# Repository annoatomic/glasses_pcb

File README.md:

KICAD projects saved in: flex_mems

flex_aufsatz project in: flex_mems
                      -->flex_aufsatz

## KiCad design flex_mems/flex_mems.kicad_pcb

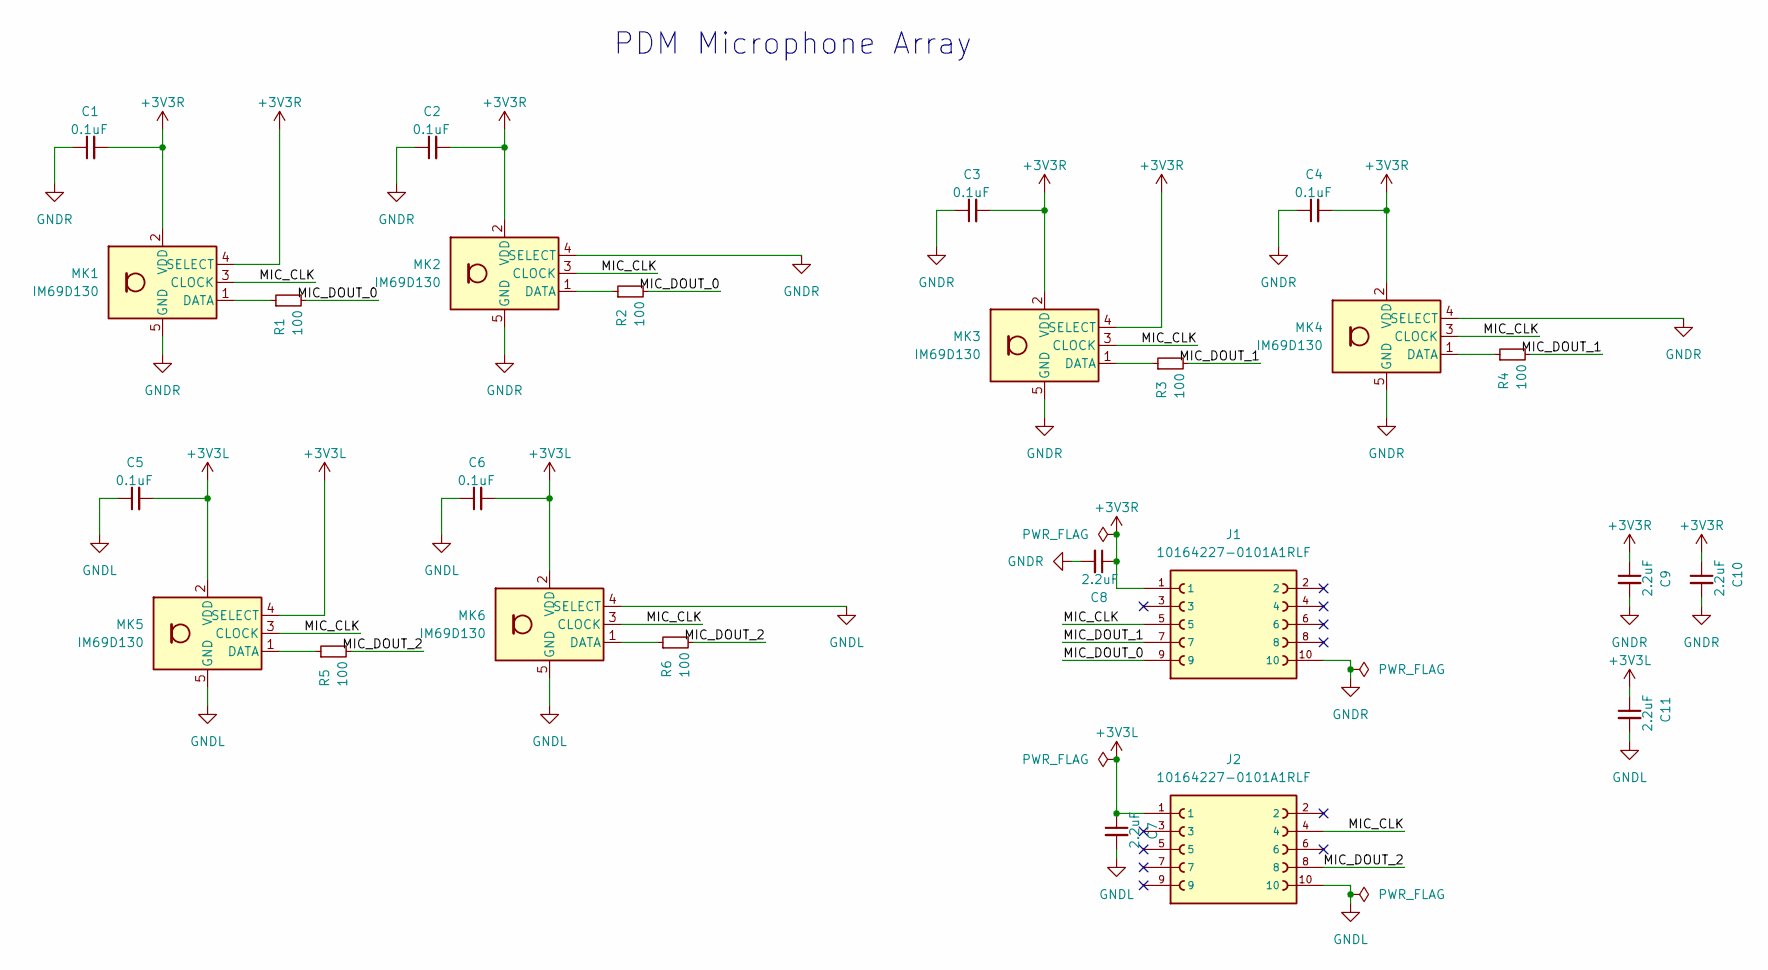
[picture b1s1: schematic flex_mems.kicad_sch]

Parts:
C1, C2, C3, C4, C5, C6: 0.1uF; C_0402_1005Metric
C7, C8, C9, C10, C11: 2.2uF; C_0402_1005Metric
J1, J2: 10164227-0101A1RLF; AMPHENOL_10164227-0101A1RLF; PARTREV C
MK1, MK2, MK3, MK4, MK5, MK6: IM69D130; Infineon_PG-LLGA-5-1
R1, R2, R3, R4, R5, R6: 100; R_0402_1005Metric

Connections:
+3V3L: C5.2, C6.2, C7.1, C11.1, J2.1, MK5.2 (VDD), MK5.4 (SELECT), MK6.2 (VDD)
+3V3R: C1.2, C2.2, C3.2, C4.2, C8.1, C9.1, C10.1, J1.1, MK1.2 (VDD), MK1.4 (SELECT), MK2.2 (VDD), MK3.2 (VDD), MK3.4 (SELECT), MK4.2 (VDD)
/MIC_CLK: J1.5, J2.4, MK1.3 (CLOCK), MK2.3 (CLOCK), MK3.3 (CLOCK), MK4.3 (CLOCK), MK5.3 (CLOCK), MK6.3 (CLOCK)
/MIC_DOUT_0: J1.9, R1.2, R2.2
/MIC_DOUT_1: J1.7, R3.2, R4.2
/MIC_DOUT_2: J2.8, R5.2, R6.2
GNDL: C5.1, C6.1, C7.2, C11.2, J2.10, MK5.5 (GND), MK6.4 (SELECT), MK6.5 (GND)
GNDR: C1.1, C2.1, C3.1, C4.1, C8.2, C9.2, C10.2, J1.10, MK1.5 (GND), MK2.4 (SELECT), MK2.5 (GND), MK3.5 (GND), MK4.4 (SELECT), MK4.5 (GND)
unnamed: MK1.1 (DATA), R1.1
unnamed: MK2.1 (DATA), R2.1
unnamed: MK3.1 (DATA), R3.1
unnamed: MK4.1 (DATA), R4.1
unnamed: MK5.1 (DATA), R5.1
unnamed: MK6.1 (DATA), R6.1

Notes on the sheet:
PDM Microphone Array

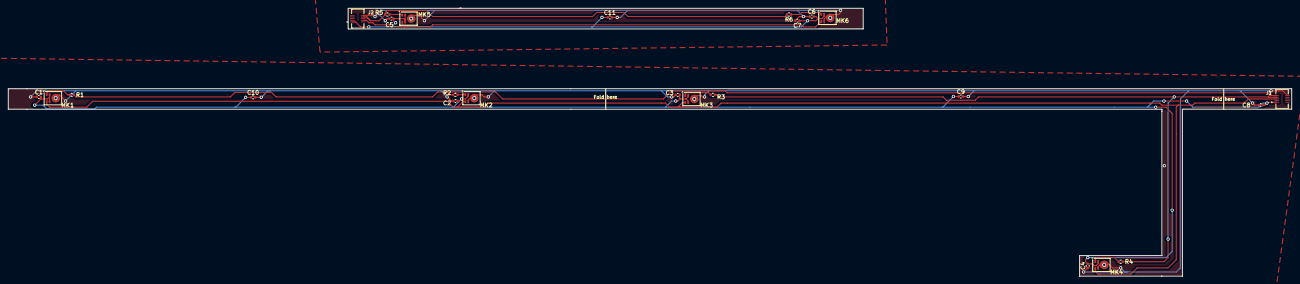
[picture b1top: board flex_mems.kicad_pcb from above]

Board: 2 copper layers, 311.5 x 65.0 mm, 25 parts (0 on the bottom side), 14 nets.

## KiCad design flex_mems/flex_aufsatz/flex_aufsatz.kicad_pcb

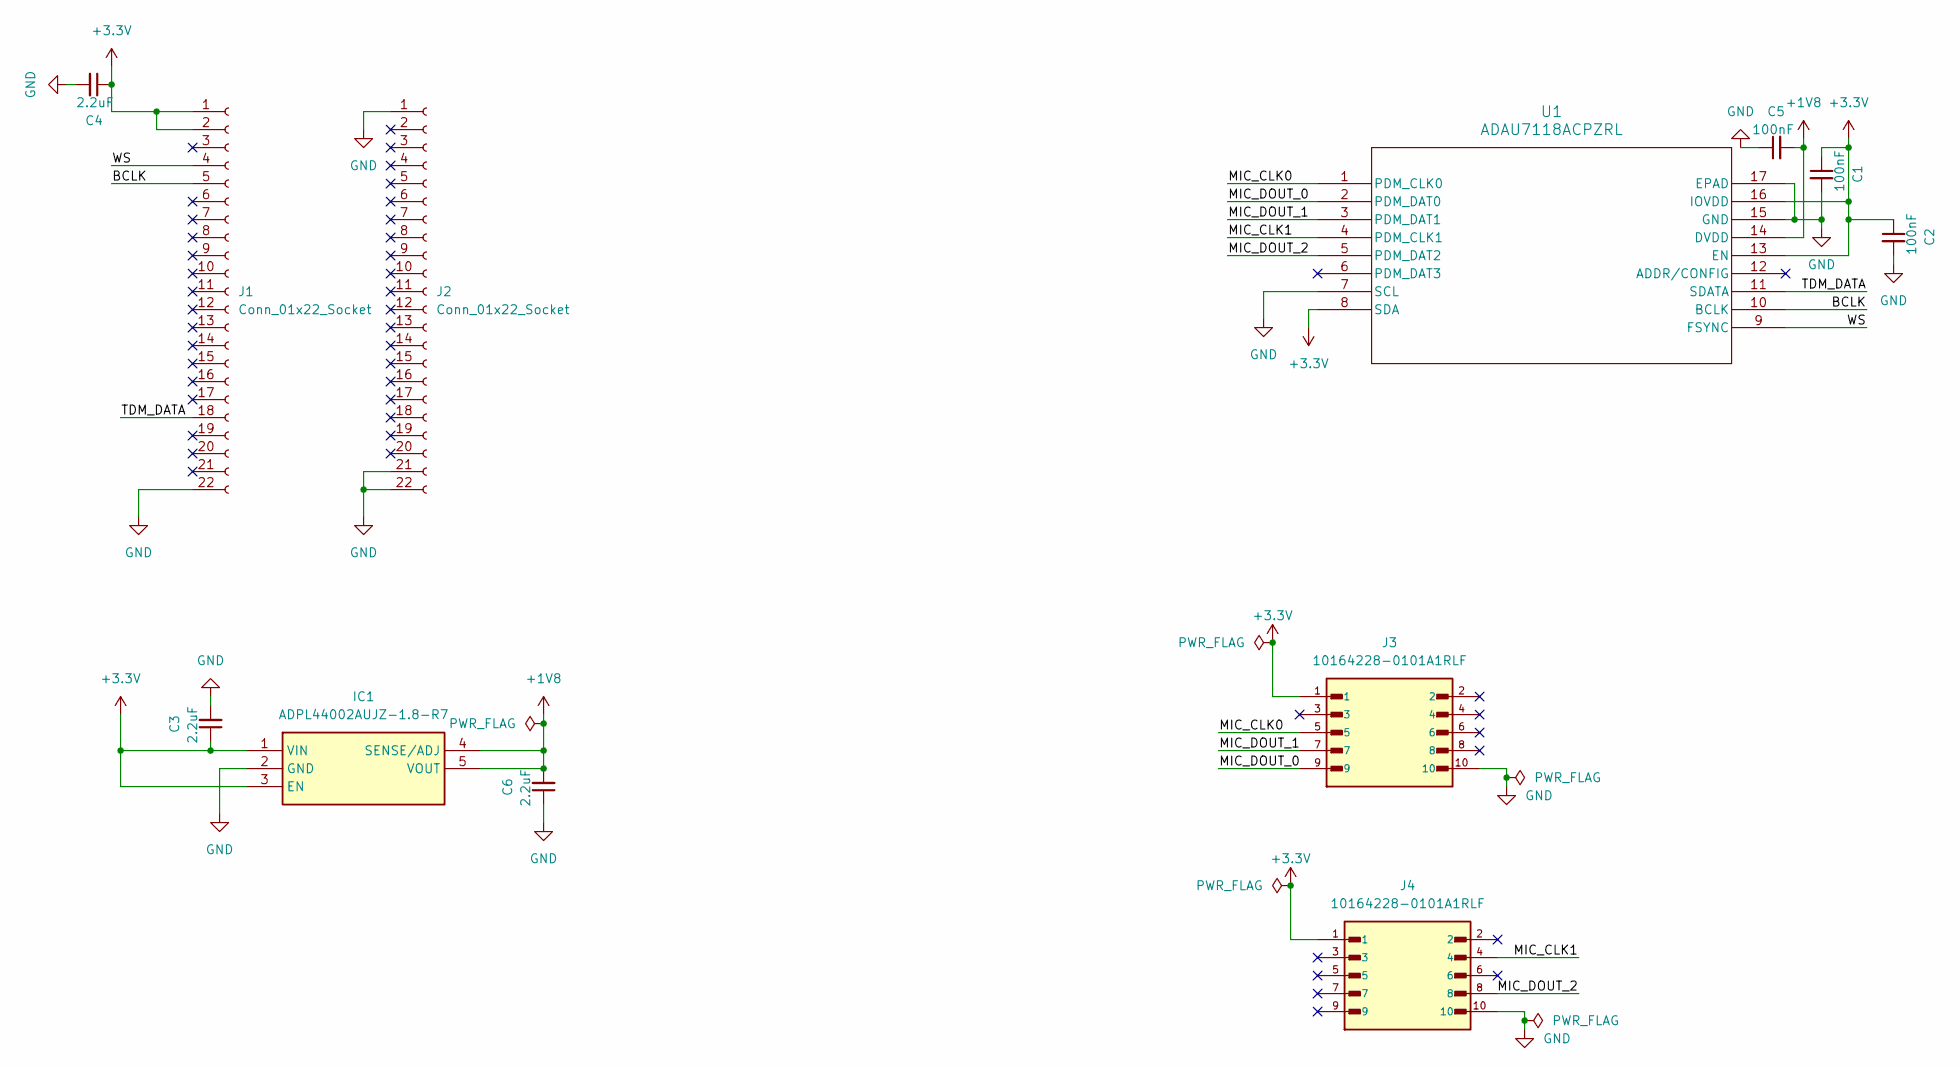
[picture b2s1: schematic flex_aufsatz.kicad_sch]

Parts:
C1, C2, C5: 100nF; C_0402_1005Metric
C3, C4, C6: 2.2uF; C_0402_1005Metric
IC1: ADPL44002AUJZ-1.8-R7; SOT95P280X100-5N; Mouser Part Number 584-PL44002AUJZ18R7
J1, J2: Conn_01x22_Socket; PinSocket_1x22_P2.54mm_Vertical
J3, J4: 10164228-0101A1RLF; AMPHENOL_10164228-0101A1RLF; PARTREV C
U1: ADAU7118ACPZRL; QFN50P300X300X80-17N-D

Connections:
+1V8: C5.2, C6.2, IC1.4 (SENSE/ADJ), IC1.5 (VOUT), U1.14 (DVDD)
+3.3V: C1.1, C2.1, C3.1, C4.1, IC1.1 (VIN), IC1.3 (EN), J1.1, J1.2, J3.1, J4.1, U1.8 (SDA), U1.13 (EN), U1.16 (IOVDD)
/BCLK: J1.5, U1.10 (BCLK)
/MIC_CLK0: J3.5, U1.1 (PDM_CLK0)
/MIC_CLK1: J4.4, U1.4 (PDM_CLK1)
/MIC_DOUT_0: J3.9, U1.2 (PDM_DAT0)
/MIC_DOUT_1: J3.7, U1.3 (PDM_DAT1)
/MIC_DOUT_2: J4.8, U1.5 (PDM_DAT2)
/TDM_DATA: J1.18, U1.11 (SDATA)
/WS: J1.4, U1.9 (FSYNC)
GND: C1.2, C2.2, C3.2, C4.2, C5.1, C6.1, IC1.2 (GND), J1.22, J2.1, J2.21, J2.22, J3.10, J4.10, U1.7 (SCL), U1.15 (GND), U1.17 (EPAD)

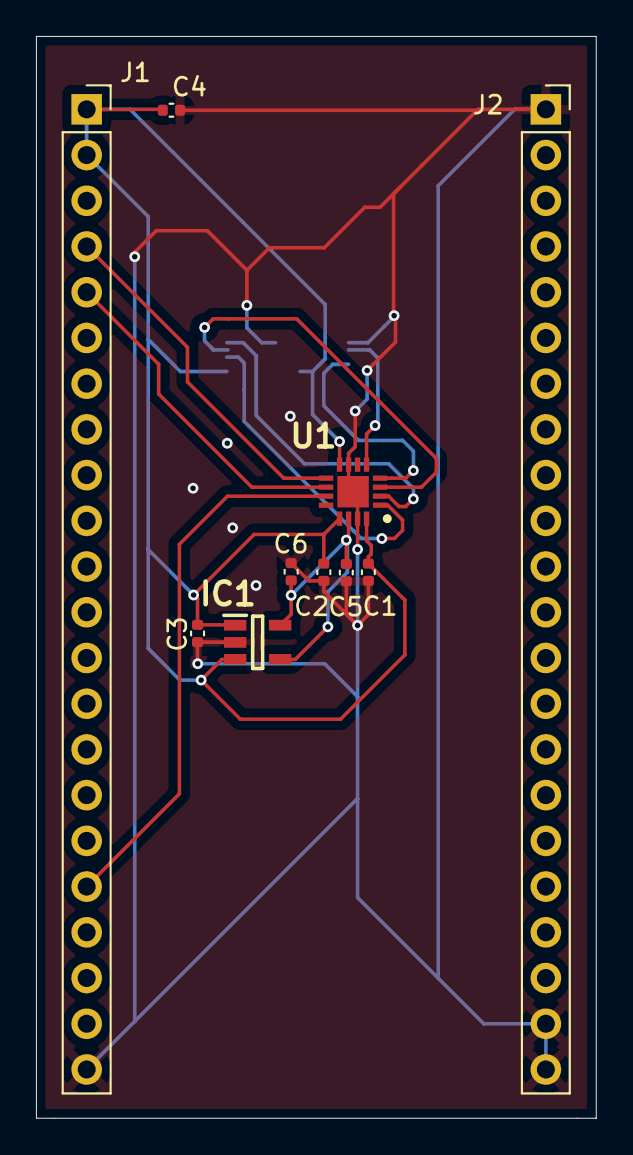
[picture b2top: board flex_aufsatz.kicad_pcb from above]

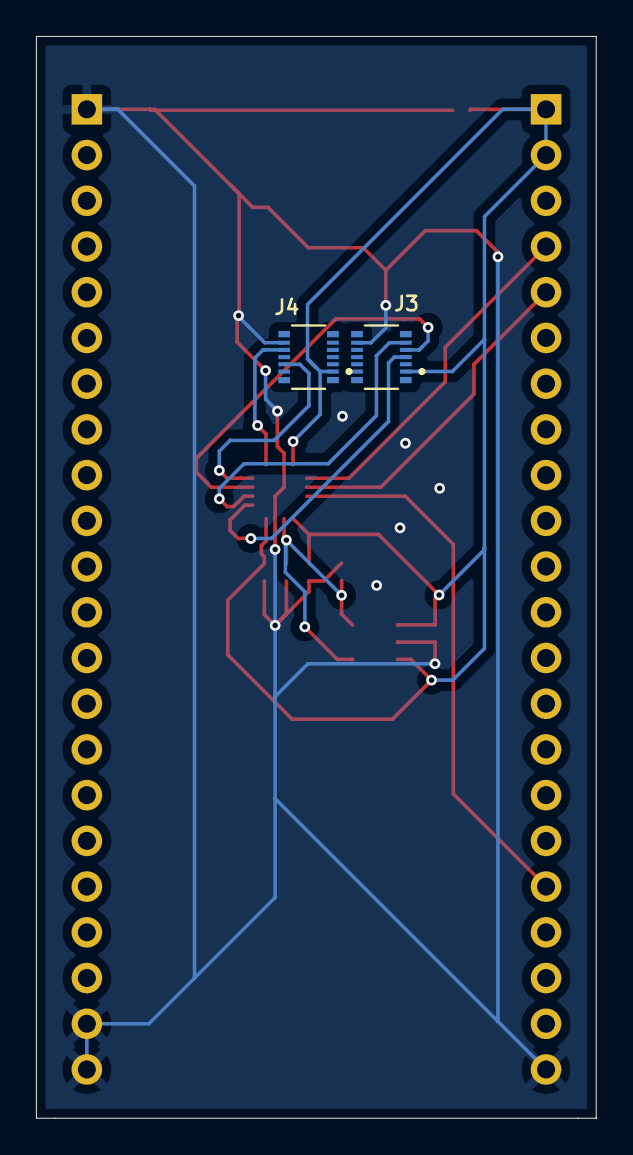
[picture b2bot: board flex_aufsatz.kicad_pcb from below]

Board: 2 copper layers, 31.1 x 60.1 mm, 12 parts (2 on the bottom side), 11 nets.

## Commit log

2025-06-26 flex header first steps
2025-06-27 Schematics done
2025-06-27 flex_aufsatz1.0
2025-06-27 small fix gbr
2025-07-01 GND zone update
2025-10-08 update funktionierende PCB mit WLAN Transport
2025-10-08 start pupil labs implementation
2025-10-11 aufgeräumt mit 2mic out
2025-10-11 all channels udp
2025-10-15 udp update with header bits
